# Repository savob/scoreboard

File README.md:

# Tools 102 Scoreboard

Scoreboard I made for the Tools 102 workshop in 2019. The goal was to bring in some electronics for people to learn with rather than just the usual mechanical stuff done. To that end I wanted to help build an electric countdown system based around an Arduino Nano which would show the time and keep track of score.

# Hardware

For this project I made the main board and a friend did the auxiliary detector board, both were designed to make the most of the back layer since these boards were going to be milled on campus, not etched in a factory. Thus there would be no plated through holes so keeping everything on the back made soldering and connections easier.

The boards were originally designed in EAGLE, but have since been converted to KiCad 7.0.10.

# Software

The code focused on the display function, and was all written in the Arduino IDE 1.8.13.

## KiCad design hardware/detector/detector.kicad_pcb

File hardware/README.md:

# Hardware

Both these boards were made in EAGLE, but are now in KiCad (7.0.10) format. 

`detector` was meant to pickup a ball passing over a switch and make a single pulse using a 555 timer in monostable mode. A friend made this board.

`timeboard` was meant to be the main board for the system which would actually keep track of the score and display information like time remaining on the display for players to see.

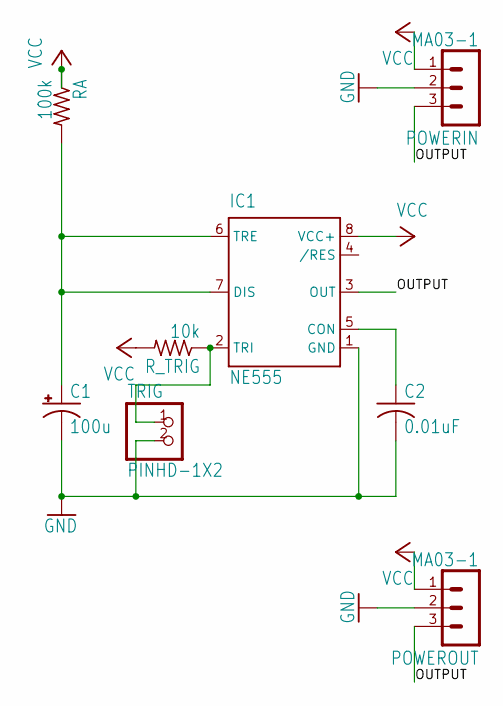
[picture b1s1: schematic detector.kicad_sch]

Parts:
C1: 100u; E3,5-8
C2: 0.01uF; C050-024X044
IC1: NE555; DIL-08
POWERIN: MA03-1
POWEROUT: MA03-1
RA: 100k; 0207_12
R_TRIG: 10k; 0207_12
TRIG: PINHD-1X2; 1X02

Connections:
GND: C1.-, C2.2, IC1.1 (GND), POWERIN.2, POWEROUT.2, TRIG.2
unnamed: C1.+, IC1.6 (TRE), IC1.7 (DIS), RA.2
unnamed: C2.1, IC1.5 (CON)
unnamed: IC1.2 (TRI), R_TRIG.1, TRIG.1
OUTPUT: IC1.3 (OUT), POWERIN.3, POWEROUT.3
VCC: IC1.8 (VCC+), POWERIN.1, POWEROUT.1, RA.1, R_TRIG.2

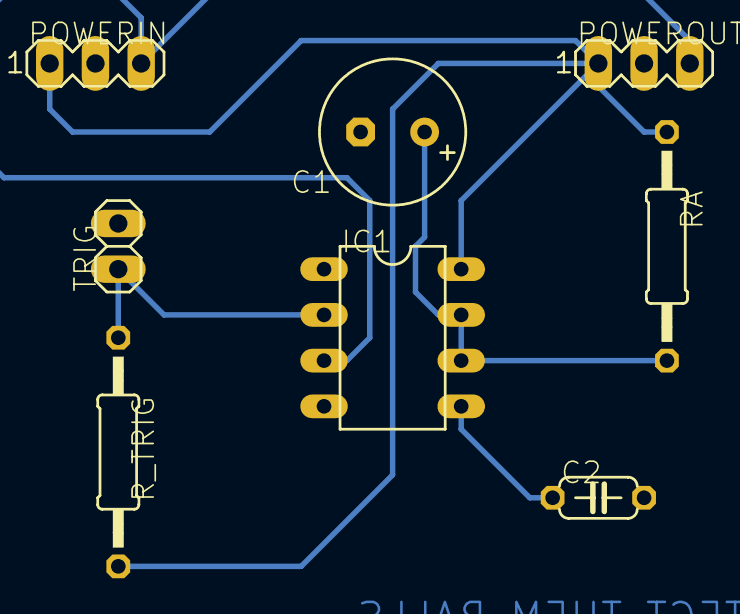
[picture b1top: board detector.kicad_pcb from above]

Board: 2 copper layers, 12 parts (0 on the bottom side), 6 nets.

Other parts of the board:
@HOLE0, @HOLE1, @HOLE2, @HOLE3: (no value)

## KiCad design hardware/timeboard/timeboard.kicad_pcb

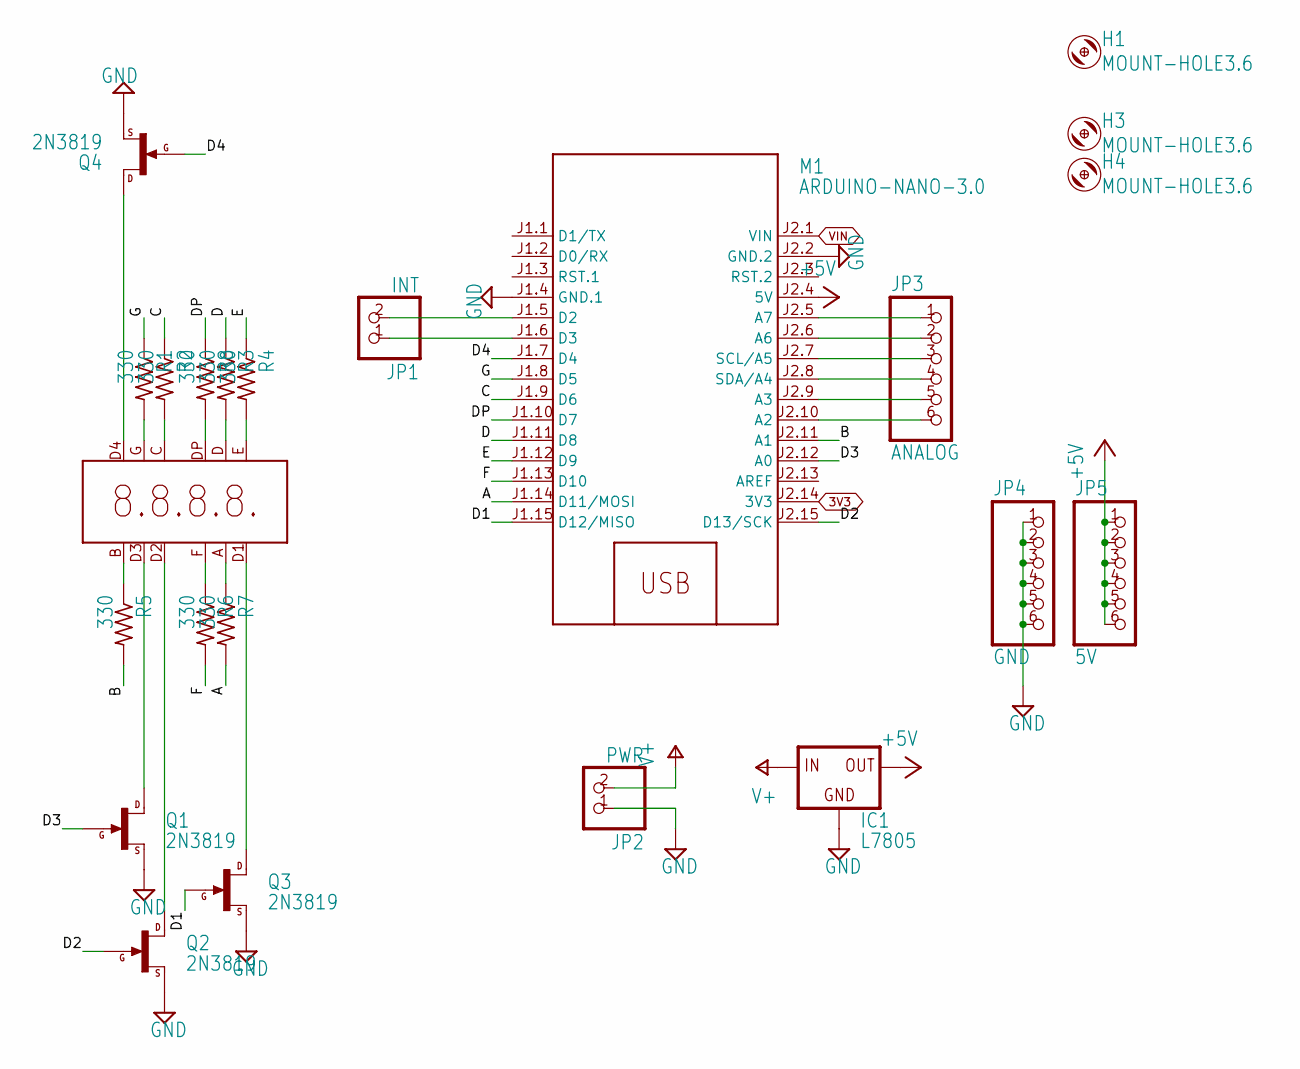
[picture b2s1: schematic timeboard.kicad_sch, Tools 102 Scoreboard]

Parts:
H1, H3, H4: MOUNT-HOLE3.6; 3,6
IC1: L7805; 78XXS
JP1: INT; 1X02
JP2: PWR; 1X02
JP3: ANALOG; 1X06
JP4: GND; 1X06
JP5: 5V; 1X06
LED1: 7SEG20MM
M1: ARDUINO-NANO-3.0
Q1, Q2, Q3, Q4: 2N3819; TO92F
R1, R2, R3, R4, R5, R6, R7, R8: 330; 0204_5

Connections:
3V3: M1.J2.14 (3V3)
+5V: IC1.OUT, JP5.1, JP5.2, JP5.3, JP5.4, JP5.5, JP5.6, M1.J2.4 (5V)
A: M1.J1.14 (D11/MOSI), R7.2
B: M1.J2.11 (A1), R5.2
C: M1.J1.9 (D6), R2.1
D: M1.J1.11 (D8), R3.1
D1: M1.J1.15 (D12/MISO), Q3.G
D2: M1.J2.15 (D13/SCK), Q2.G
D3: M1.J2.12 (A0), Q1.G
D4: M1.J1.7 (D4), Q4.G
DP: M1.J1.10 (D7), R8.1
E: M1.J1.12 (D9), R4.1
F: M1.J1.13 (D10), R6.2
G: M1.J1.8 (D5), R1.1
GND: IC1.GND, JP2.1, JP4.1, JP4.2, JP4.3, JP4.4, JP4.5, JP4.6, M1.J1.4 (GND.1), M1.J2.2 (GND.2), Q1.S, Q2.S, Q3.S, Q4.S
unnamed: LED1.D4, Q4.D
unnamed: LED1.G, R1.2
unnamed: LED1.C, R2.2
unnamed: LED1.D, R3.2
unnamed: LED1.E, R4.2
unnamed: LED1.DP, R8.2
unnamed: LED1.F, R6.1
unnamed: LED1.A, R7.1
unnamed: LED1.B, R5.1
unnamed: LED1.D3, Q1.D
unnamed: LED1.D2, Q2.D
unnamed: LED1.D1, Q3.D
unnamed: JP1.1, M1.J1.6 (D3)
unnamed: JP1.2, M1.J1.5 (D2)
unnamed: JP3.1, M1.J2.5 (A7)
unnamed: JP3.2, M1.J2.6 (A6)
unnamed: JP3.3, M1.J2.7 (SCL/A5)
unnamed: JP3.4, M1.J2.8 (SDA/A4)
unnamed: JP3.5, M1.J2.9 (A3)
unnamed: JP3.6, M1.J2.10 (A2)
V+: IC1.IN, JP2.2
VIN: M1.J2.1 (VIN)

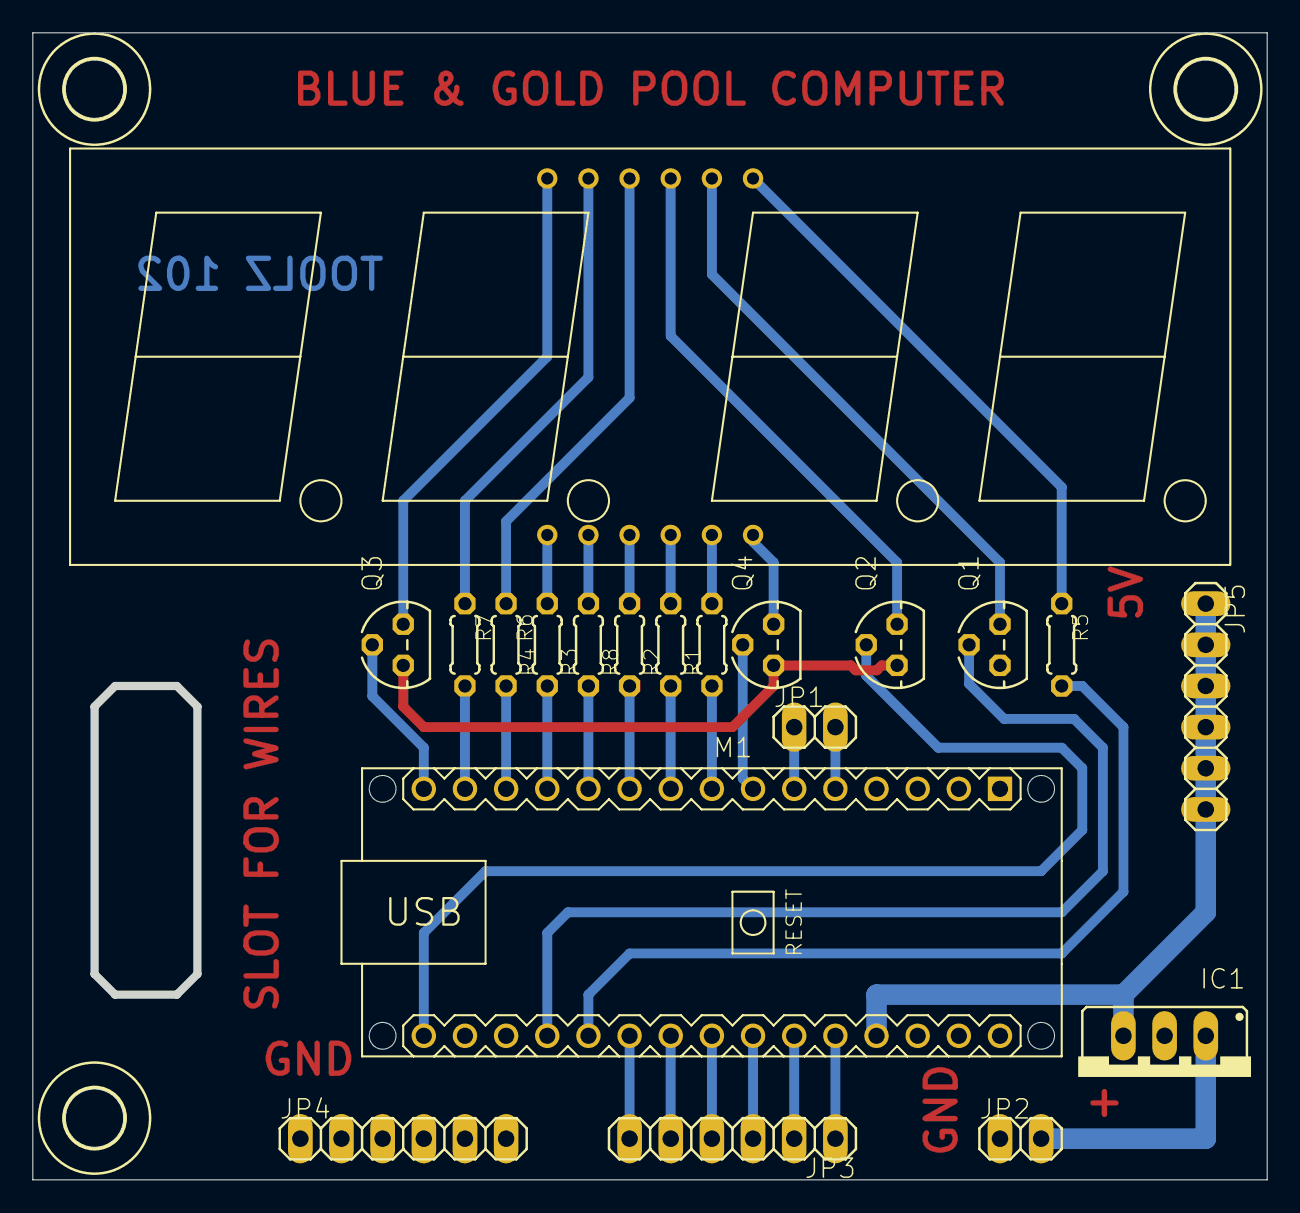
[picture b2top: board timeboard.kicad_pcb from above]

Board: 2 copper layers, 75.7 x 70.3 mm, 23 parts (0 on the bottom side), 35 nets.

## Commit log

2024-01-04 Added licence
2024-01-04 Uploaded hardware files
2024-01-04 Uploaded firmware
2024-01-04 Fixed spelling of licence file
